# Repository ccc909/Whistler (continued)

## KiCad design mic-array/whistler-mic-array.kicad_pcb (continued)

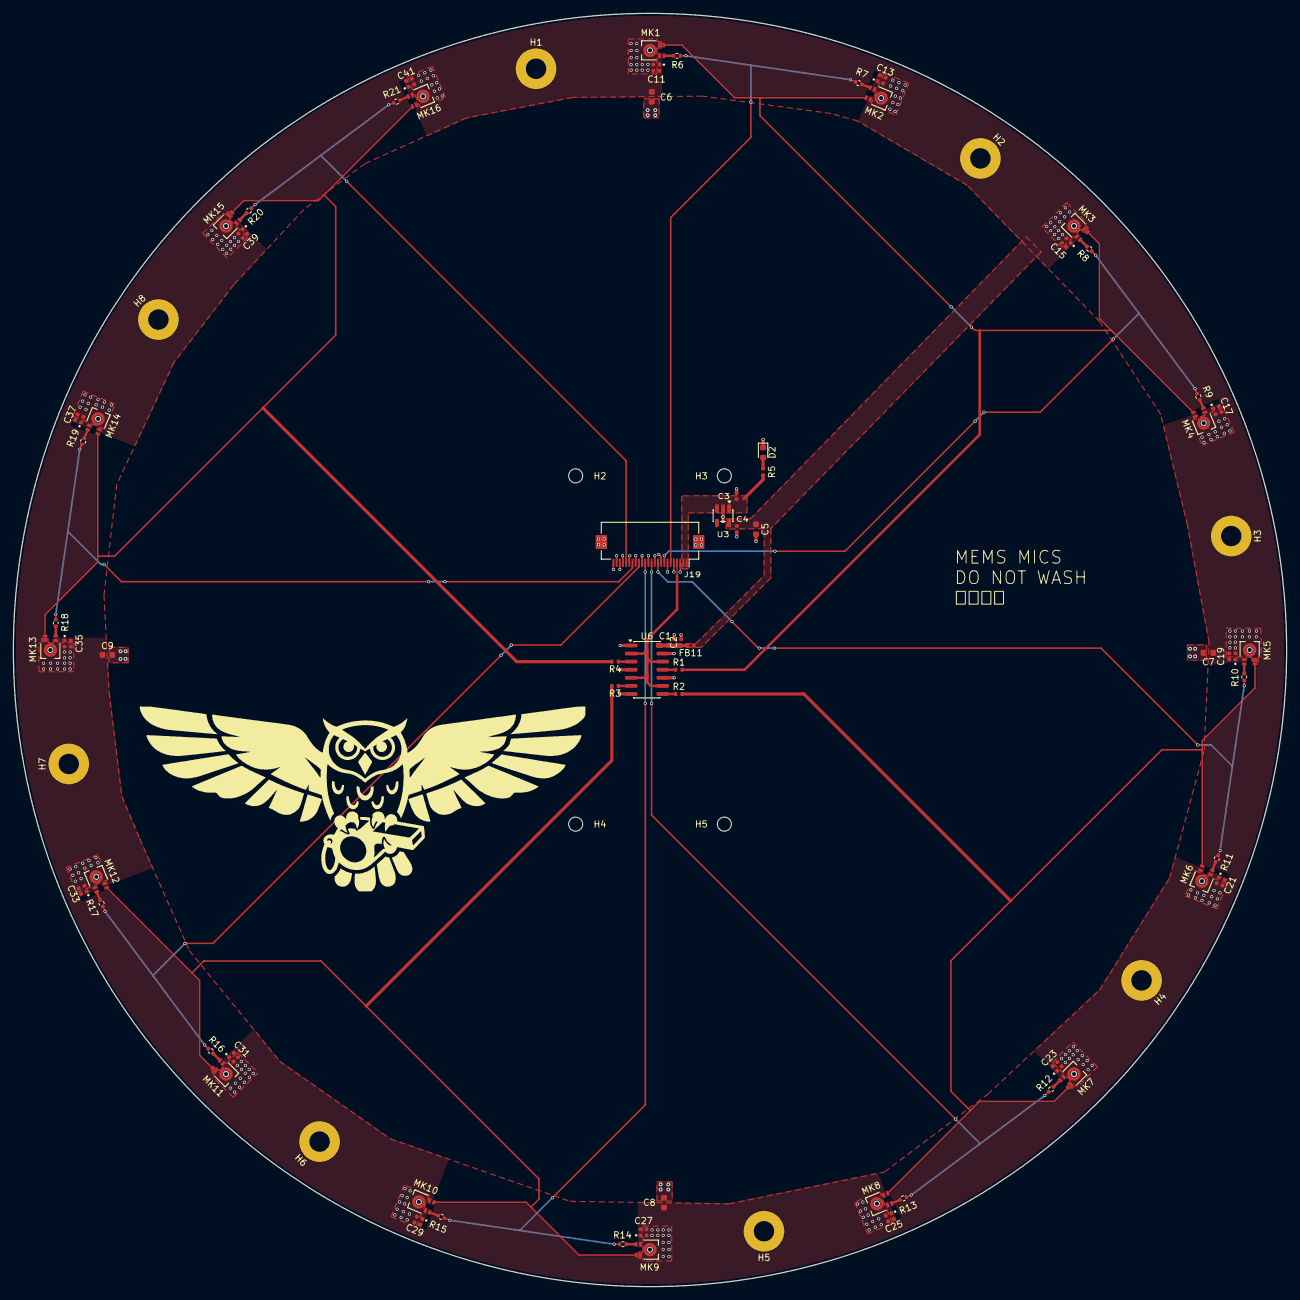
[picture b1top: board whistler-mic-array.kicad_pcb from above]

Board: 2 copper layers, 200.0 x 200.0 mm, 95 parts (0 on the bottom side), 38 nets.

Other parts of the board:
H2#2, H5#2: MountingHole_Pad; MountingHole_3.2mm_M3_Pad
H3#2, H4#2: MountingHole; MountingHole_2.2mm_M2

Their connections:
GND: H2#2.1 (1_1), H5#2.1 (1_1); also elsewhere on the board

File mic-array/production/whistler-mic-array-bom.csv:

Comment,Designator,Footprint,LCSC,Quantity,Manufacturer,MPN,Description
100nF,"C1,C12,C14,C16,C18,C20,C22,C24,C26,C28,C30,C32,C34,C36,C38,C40,C42",C_0402_1005Metric,C1525,17,,,"Unpolarized capacitor, small symbol"
1uF,"C2,C3,C4,C11,C13,C15,C17,C19,C21,C23,C25,C27,C29,C31,C33,C35,C37,C39,C41",C_0402_1005Metric,C14445,19,,,"Unpolarized capacitor, small symbol"
10uF,C5,C_0603_1608Metric,C18800,1,,,Unpolarized capacitor
4.7uF,"C6,C7,C8,C9",C_0603_1608Metric,C1705,4,,,Unpolarized capacitor
LED,D2,LED_0603_1608Metric,C12624,1,,,Light emitting diode
680R,FB11,C_0402_1005Metric,C96691,1,,,"Ferrite bead, small symbol"
Conn_01x24,J19,Hirose_FH12-24S-0.5SH_1x24-1MP_P0.50mm_Horizontal,C202112,1,,,"Generic connector, single row, 01x24, script generated (kicad-library-utils/schlib/autogen/connector/)"
IM72D128V01XTMA1,"MK1,MK2,MK3,MK4,MK5,MK6,MK7,MK8,MK9,MK10,MK11,MK12,MK13,MK14,MK15,MK16",MIC_IM72D128V01XTMA1,C5119248,16,Infineon Technologies,IM72D128,"20 Hz ~ 19 kHz Digital, PDM Microphone MEMS (Silicon) 1.62 V ~ 3.6 V Omnidirectional (-36dB ±1dB @ 94dB SPL) Solder Pads"
22R,"R1,R2,R3,R4",R_0402_1005Metric,C25092,4,,,"Resistor, small symbol"
470R,R5,R_0402_1005Metric,C25117,1,,,"Resistor, small symbol"
33R,"R6,R7,R8,R9,R10,R11,R12,R13,R14,R15,R16,R17,R18,R19,R20,R21",R_0402_1005Metric,C25105,16,,,"Resistor, small symbol"
TPS7A2018PDBVR,U3,SOT-23-5,C963430,1,,,"300 mA Low Dropout Voltage Regulator, Fixed Output, 1.6..6.0Vin, Low-Noise (7μV RMS), 6.5μA IQ LDO, SOT-23"
74LVC125,U6,SOIC-14_3.9x8.7mm_P1.27mm,C6057,1,,,Quad buffer 3-State outputs

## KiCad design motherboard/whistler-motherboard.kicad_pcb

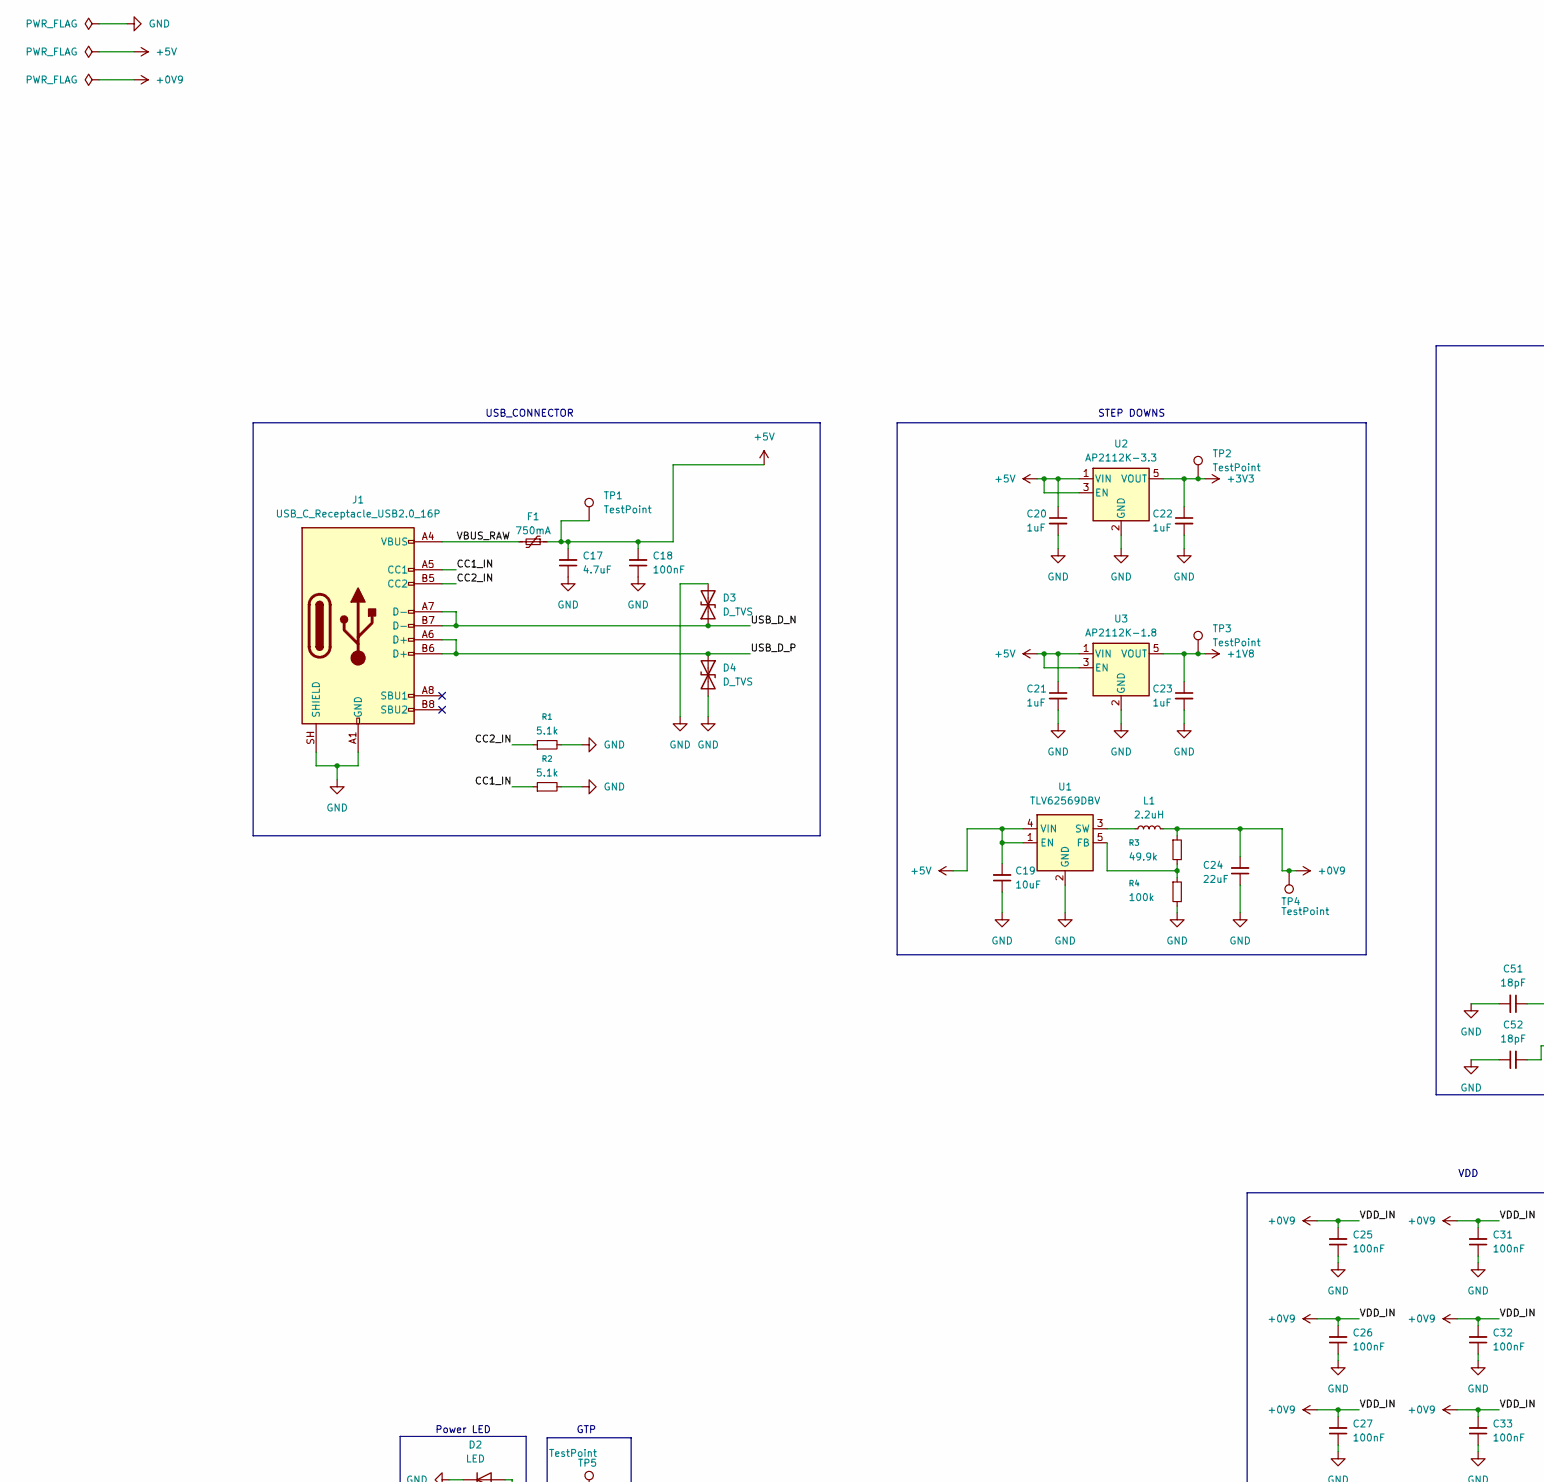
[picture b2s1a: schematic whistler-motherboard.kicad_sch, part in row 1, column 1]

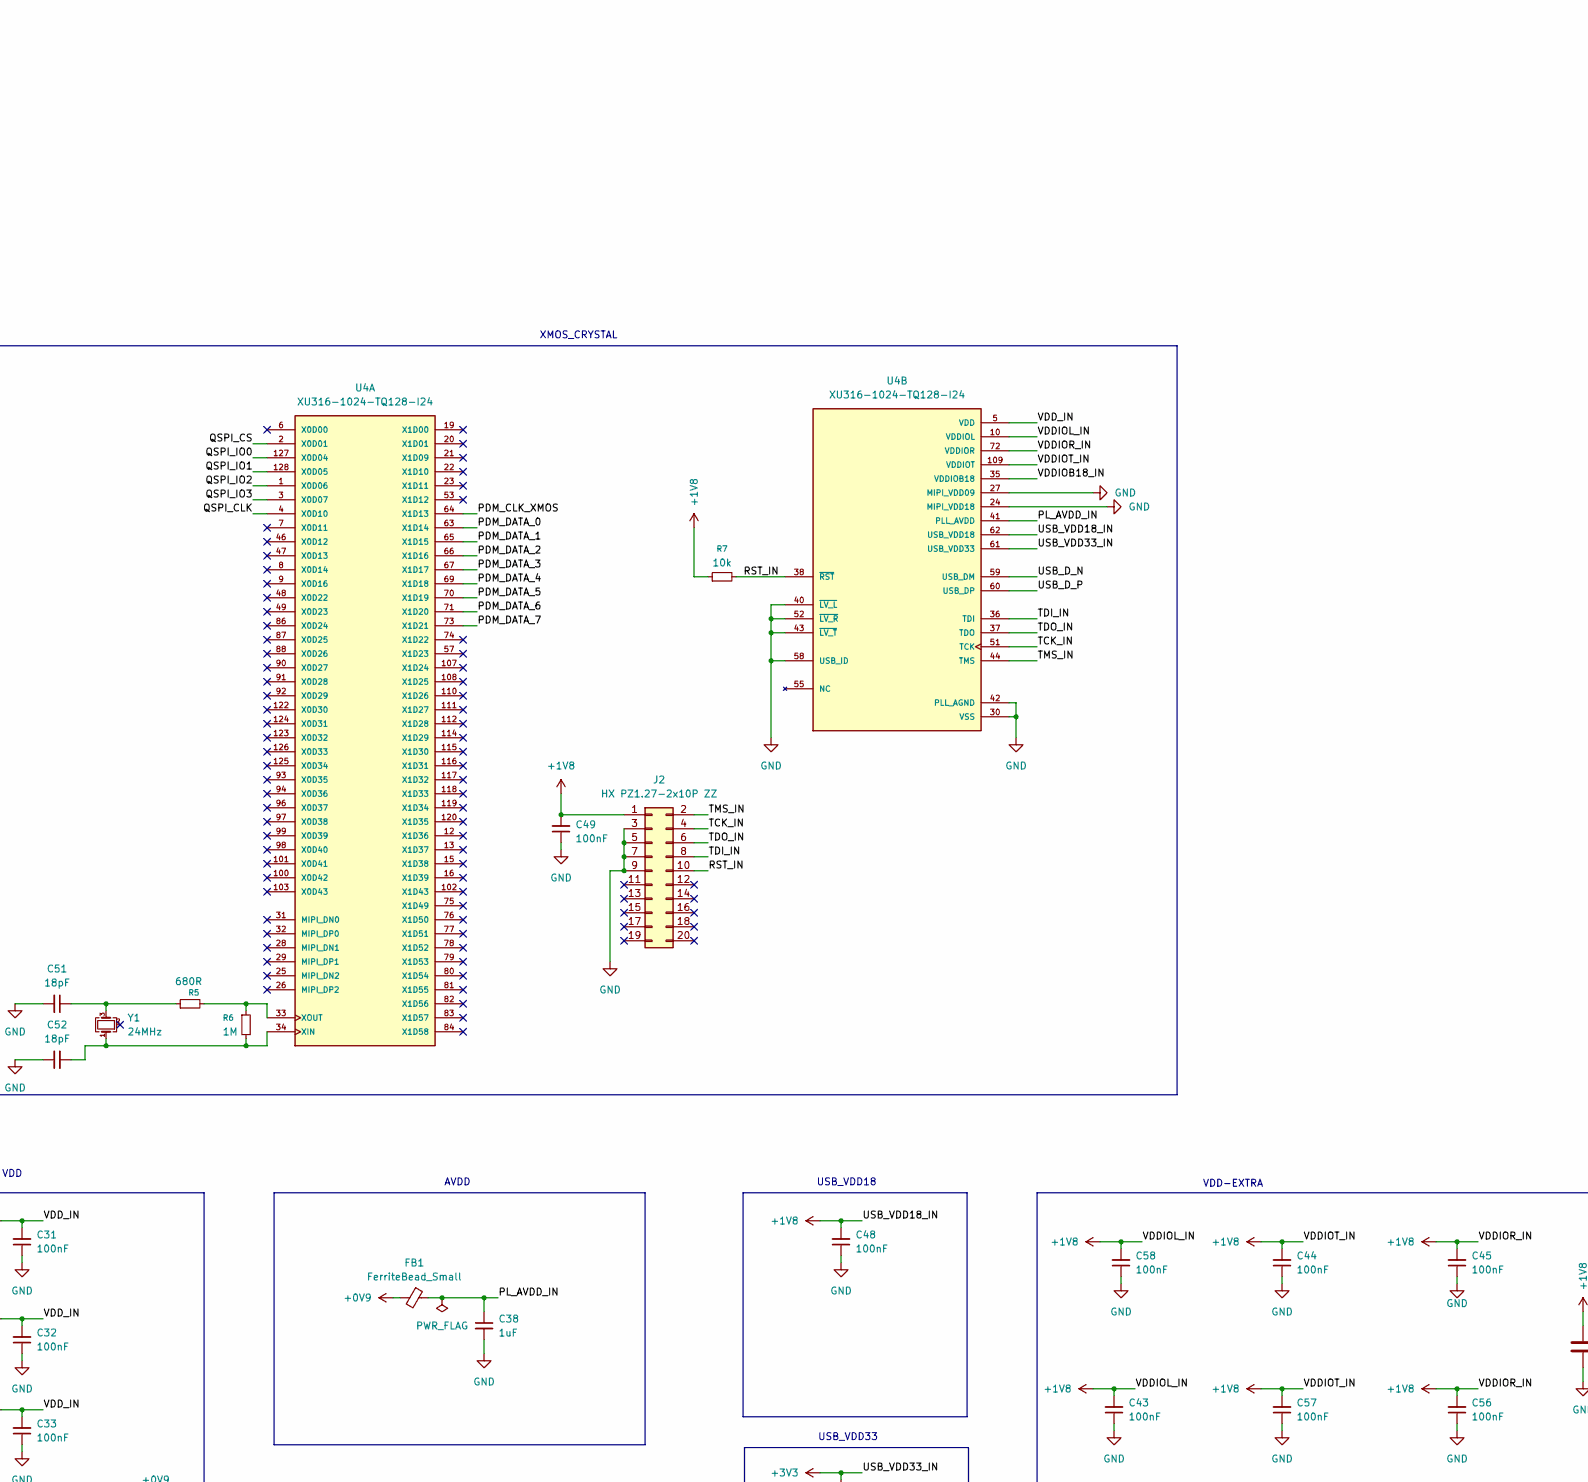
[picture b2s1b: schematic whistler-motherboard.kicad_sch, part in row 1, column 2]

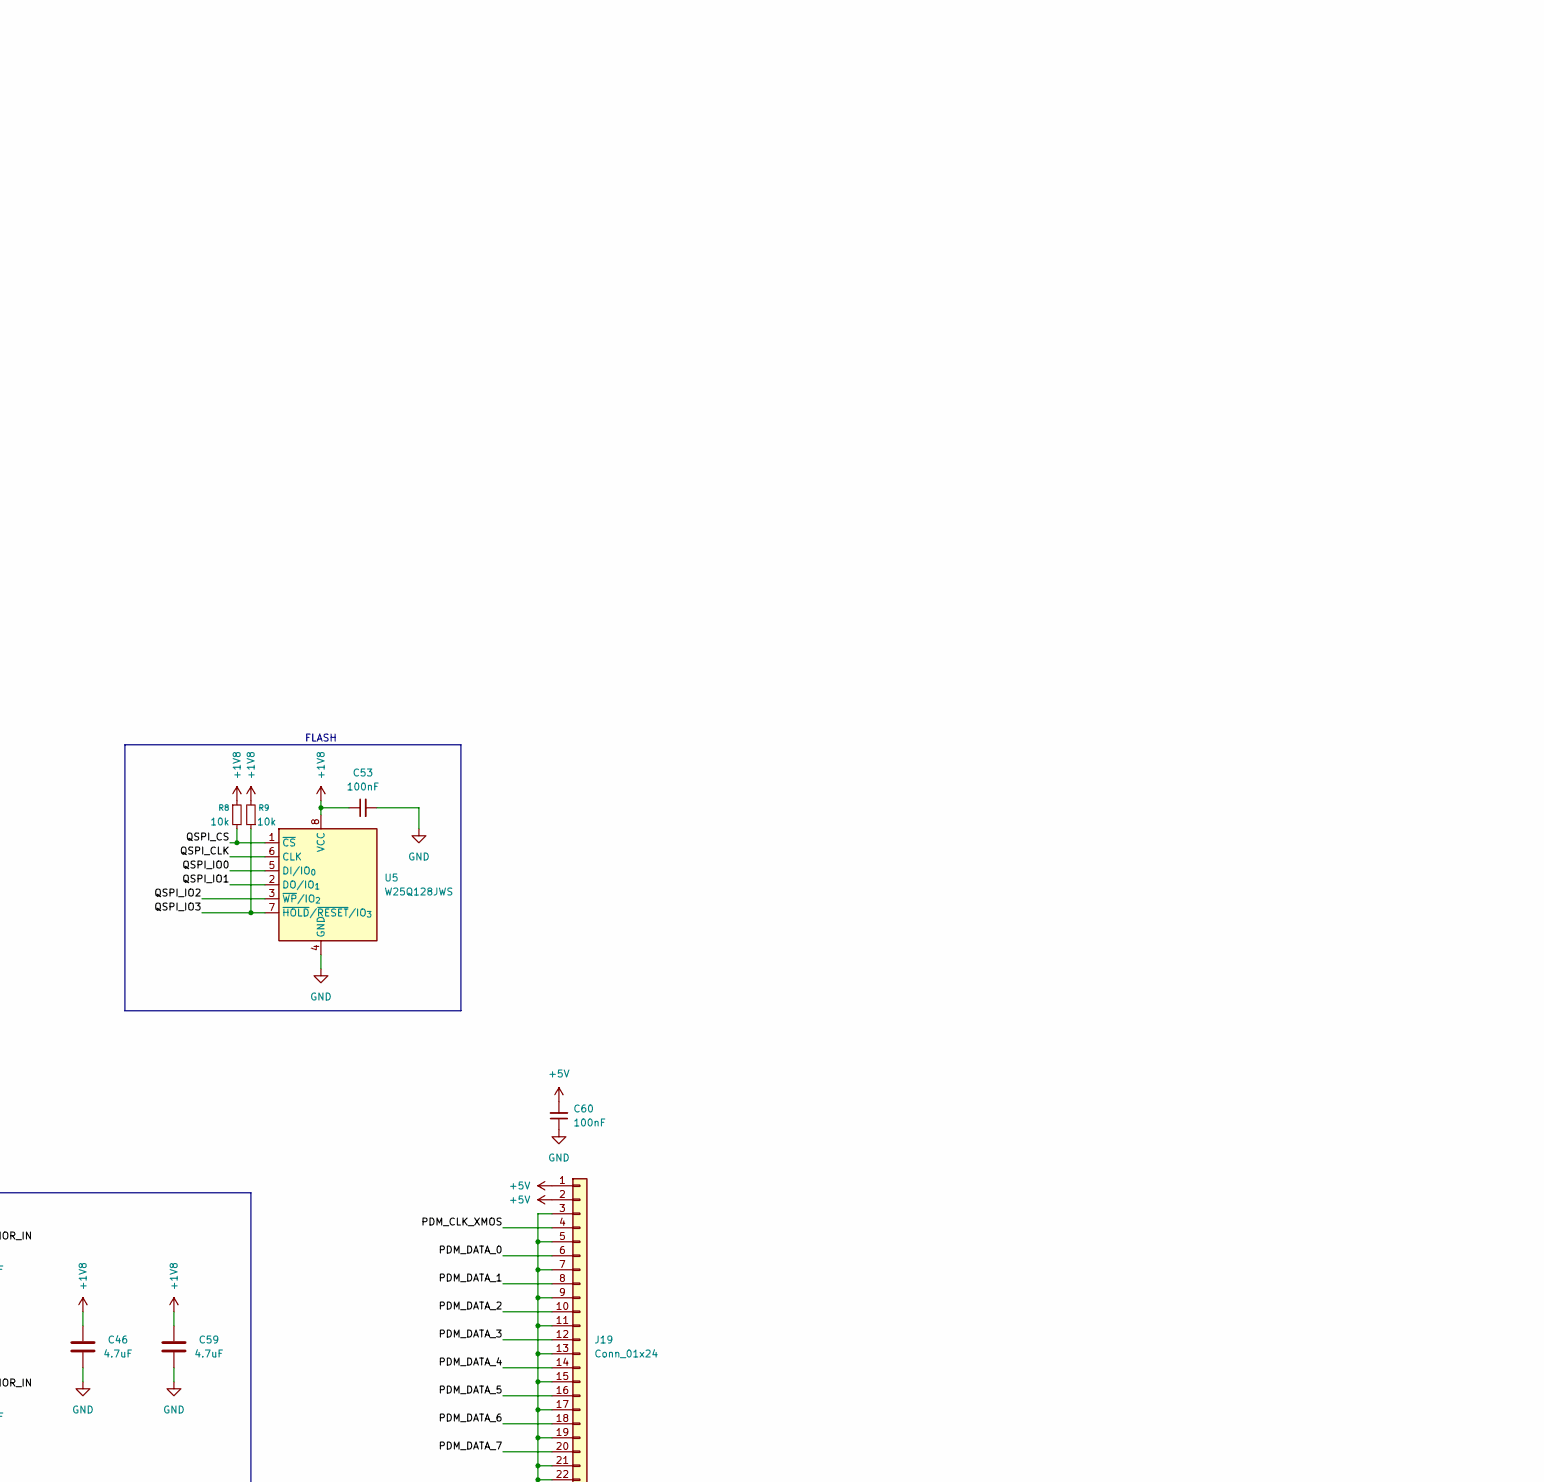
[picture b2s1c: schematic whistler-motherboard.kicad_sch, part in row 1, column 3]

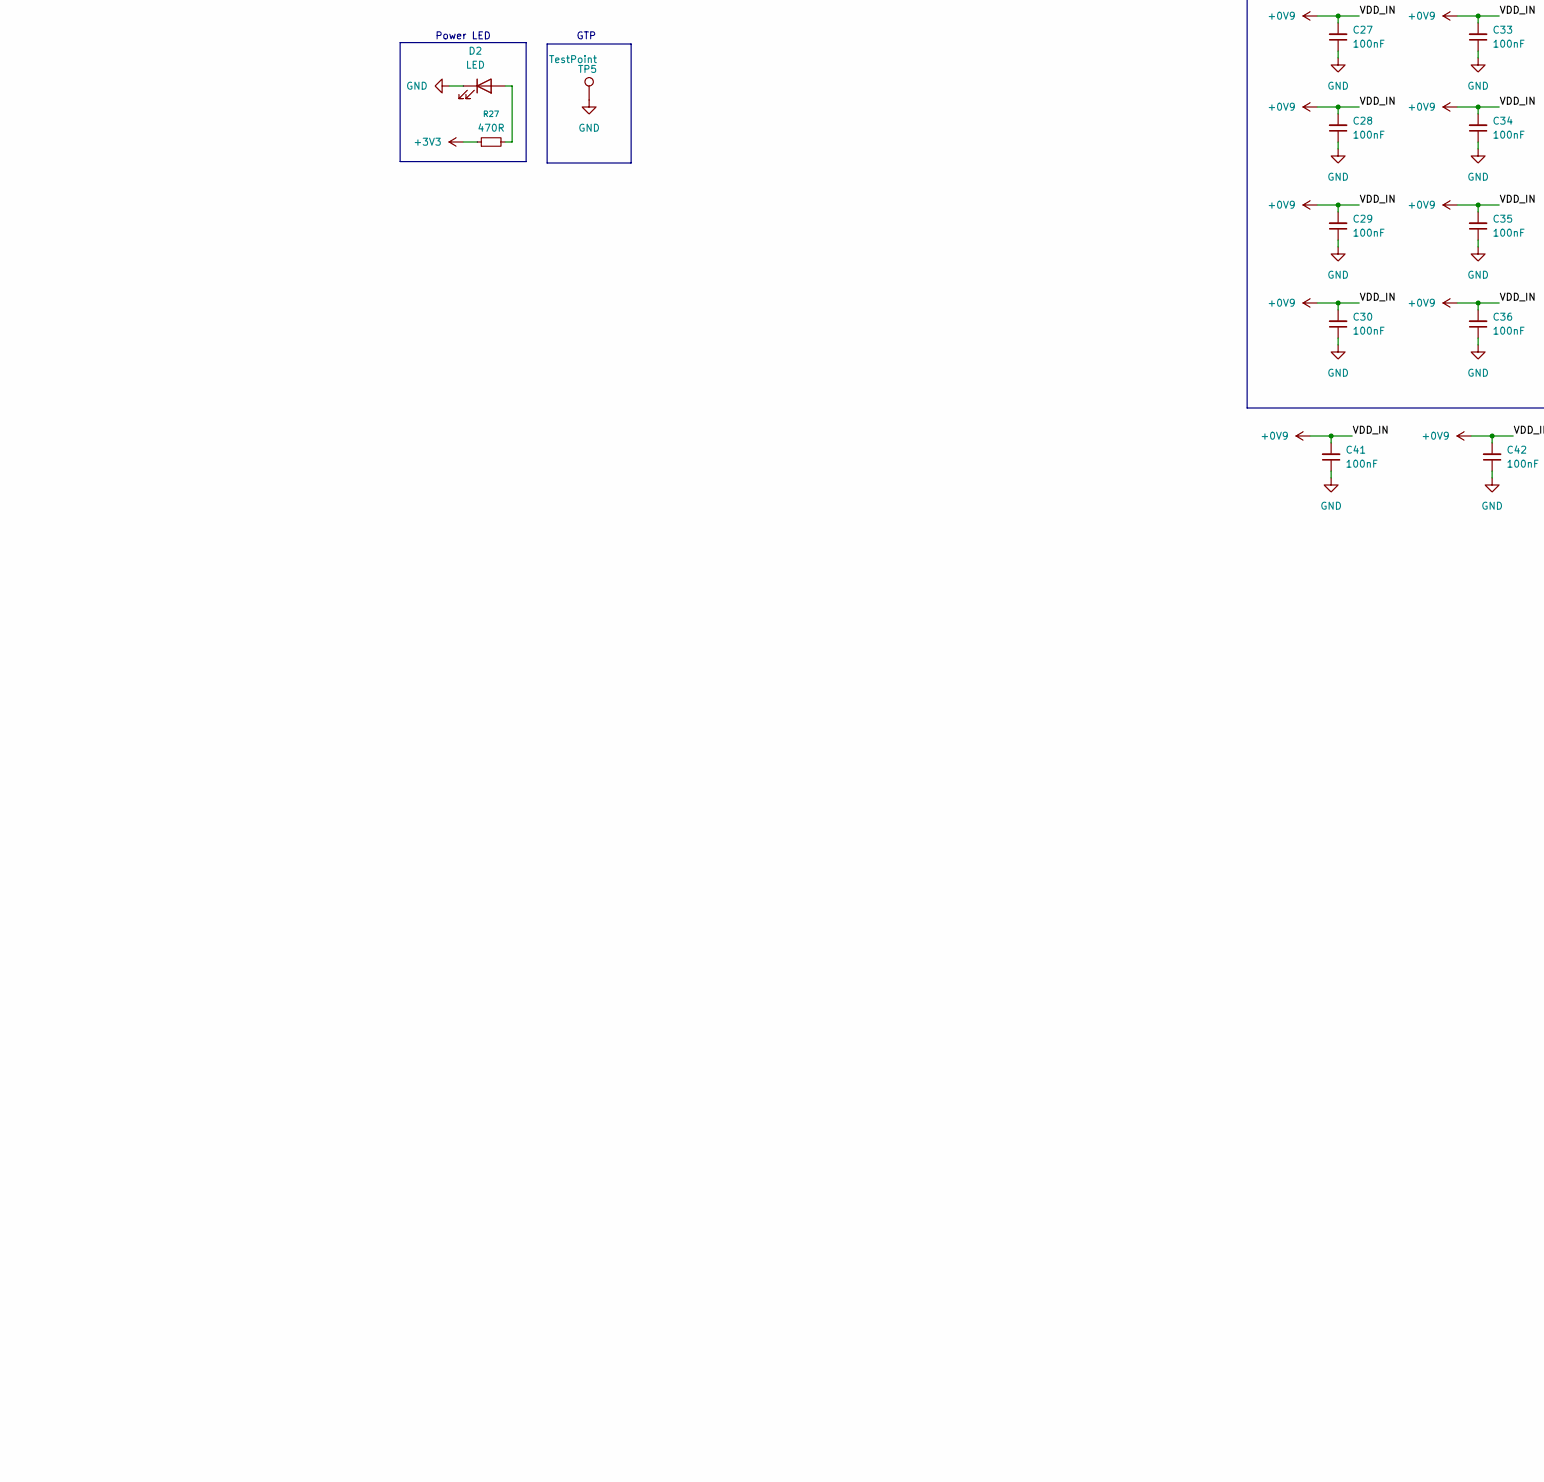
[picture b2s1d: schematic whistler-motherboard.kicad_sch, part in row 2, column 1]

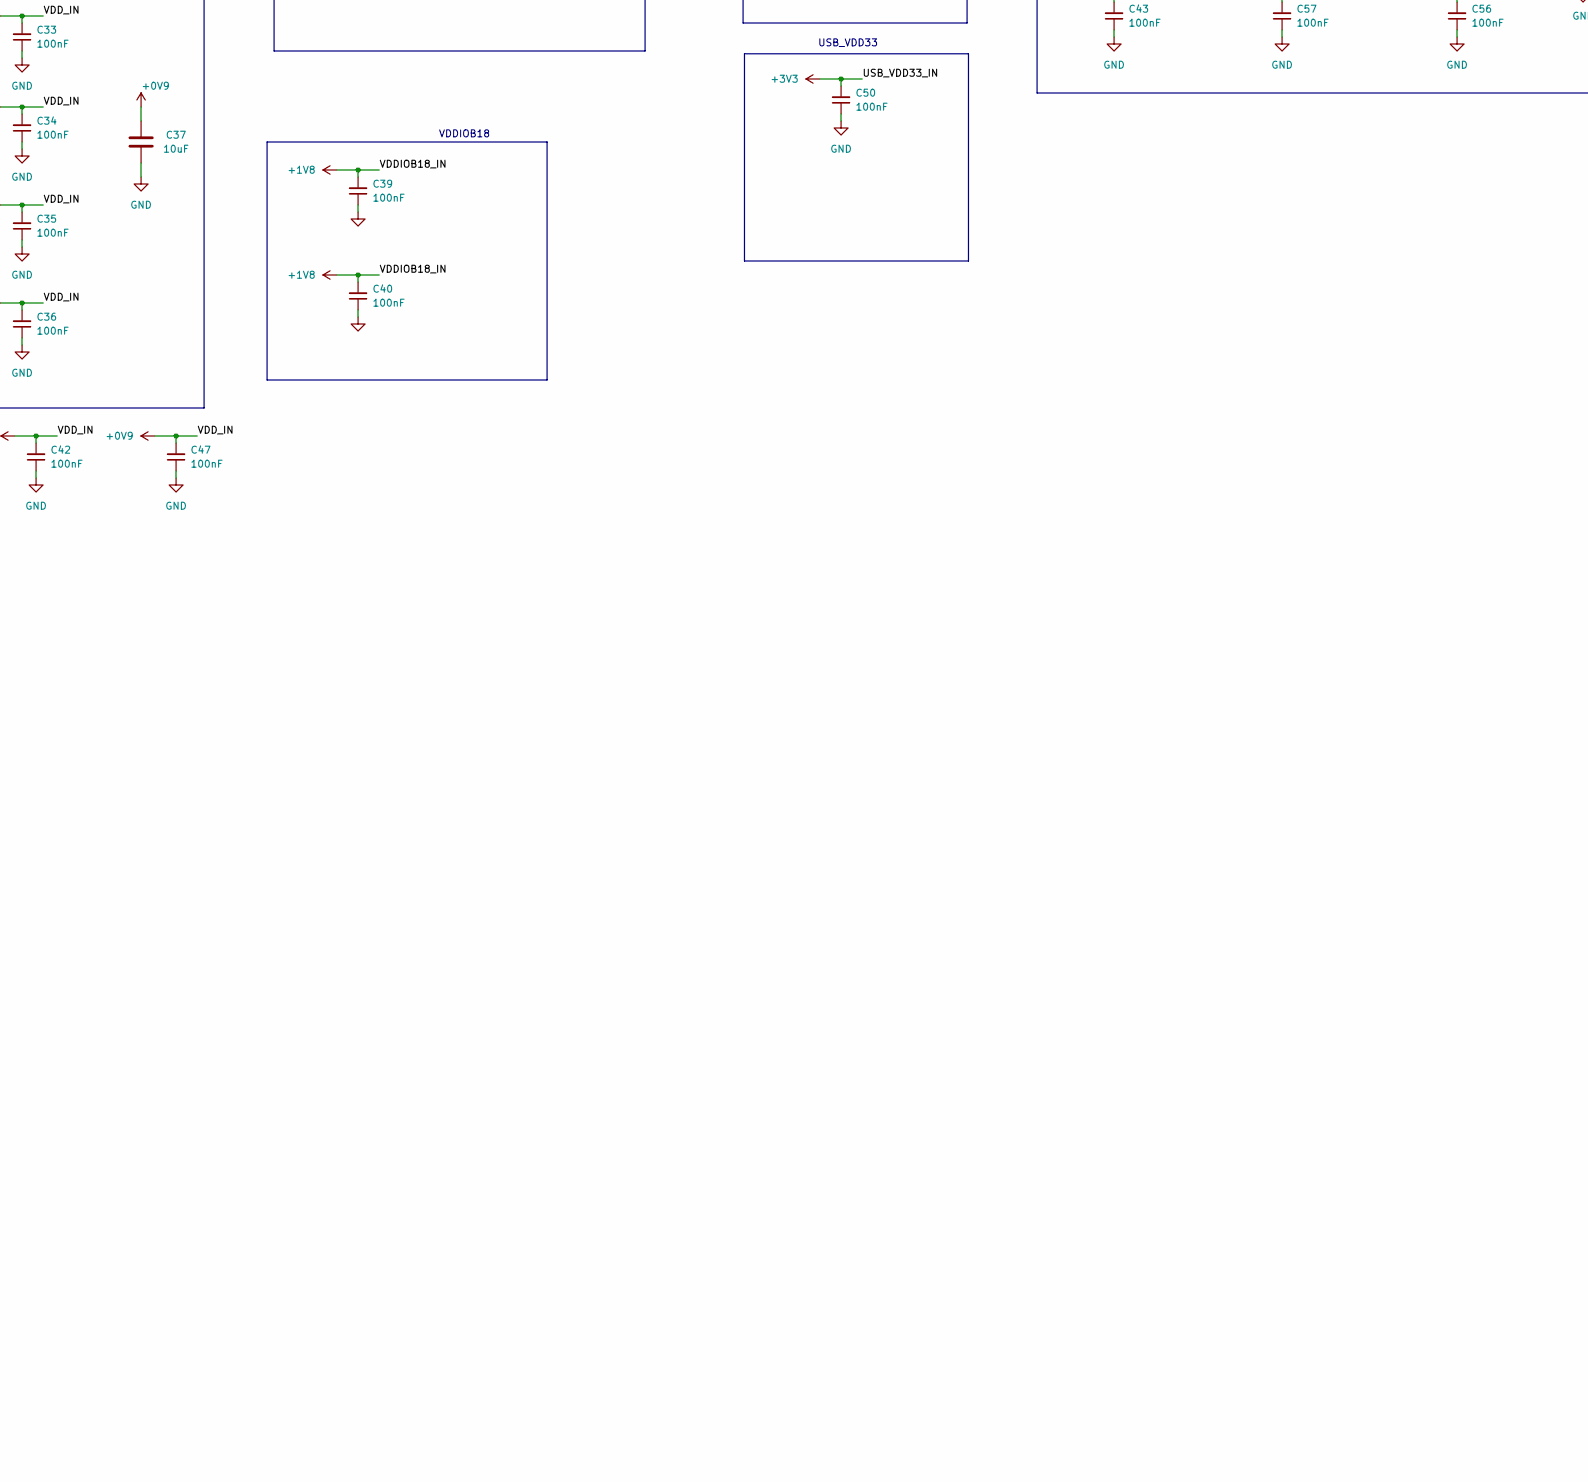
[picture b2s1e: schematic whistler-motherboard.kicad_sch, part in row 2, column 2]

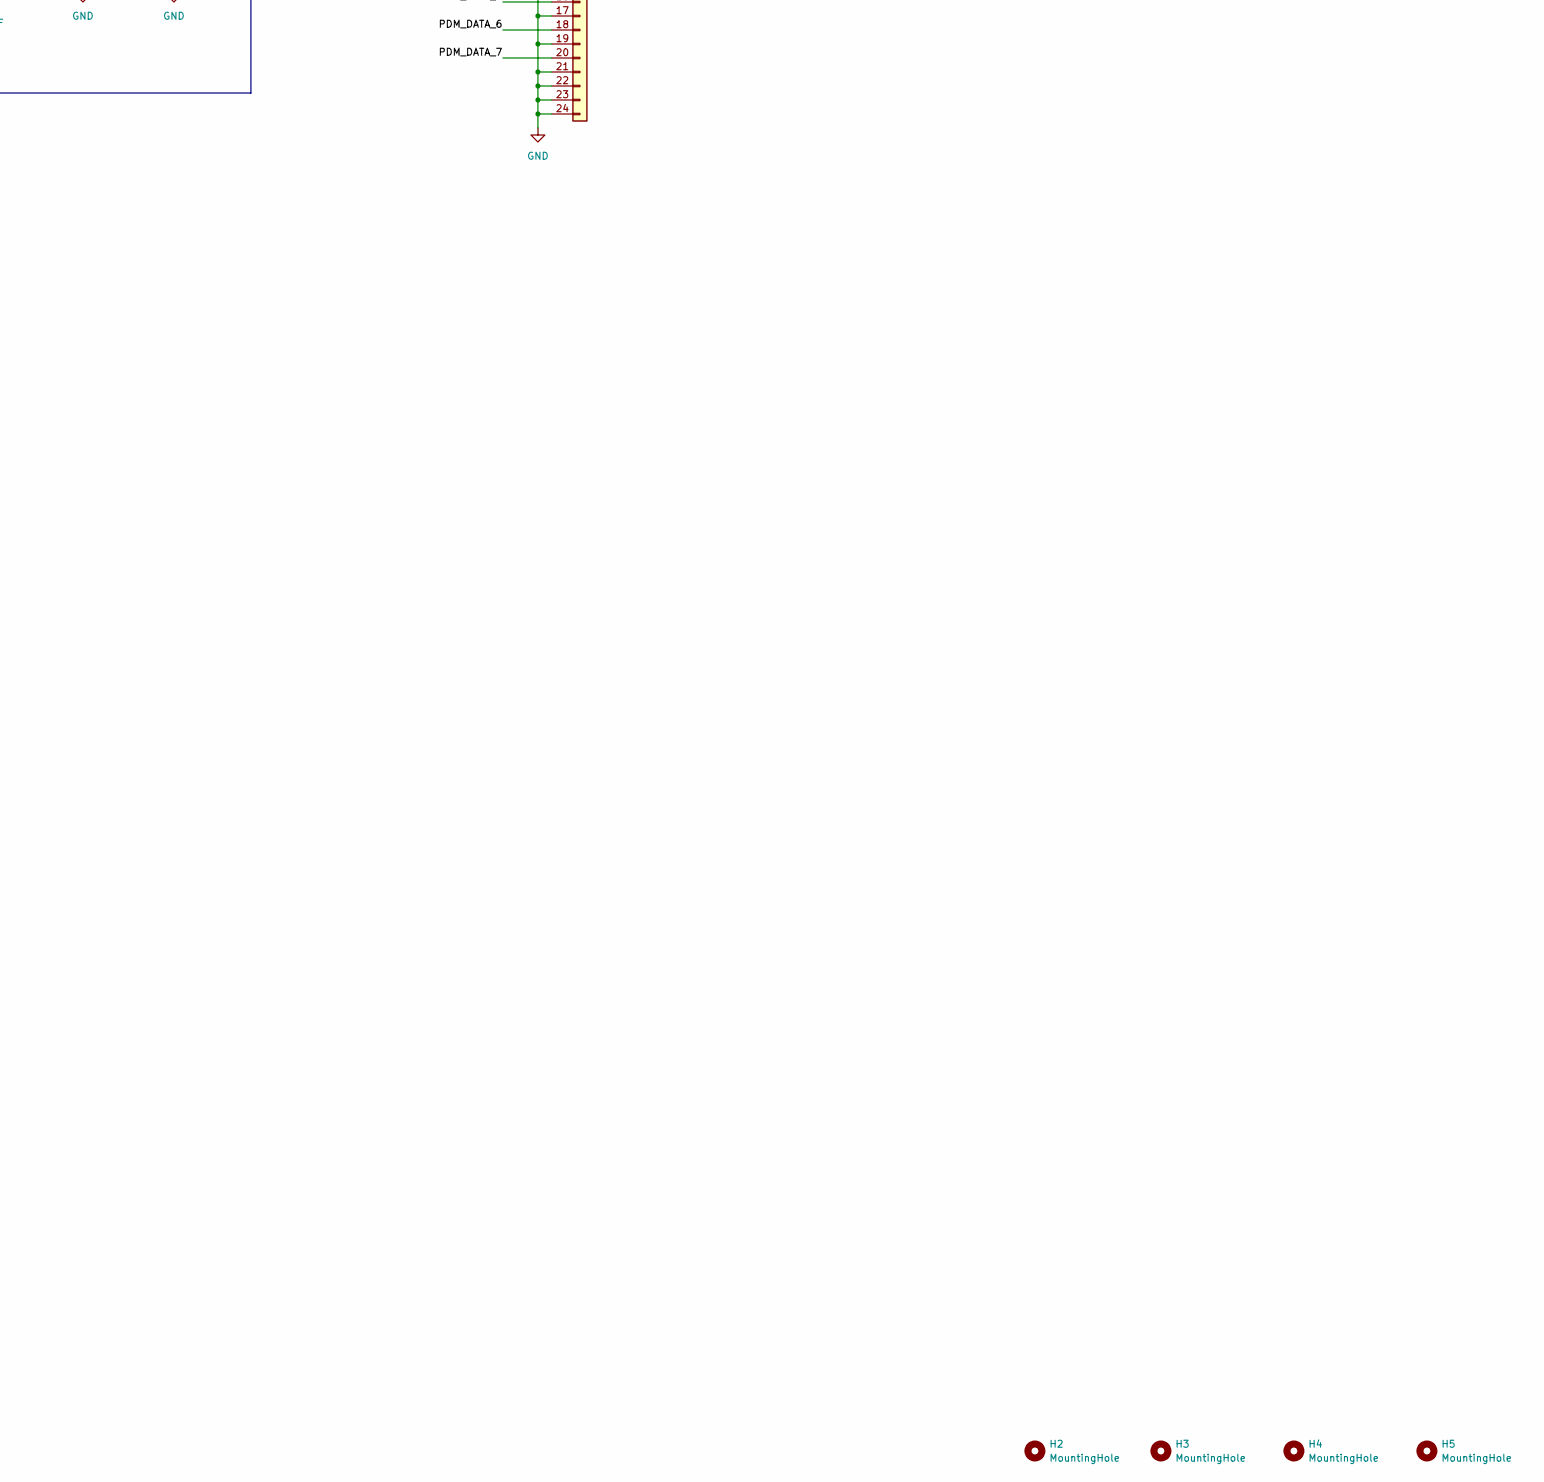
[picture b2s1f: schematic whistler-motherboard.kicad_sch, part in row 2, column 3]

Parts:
C17, C46, C59: 4.7uF; C_0603_1608Metric; LCSC C1705
C18, C25, C26, C27, C28, C29, C30, C31, C32, C33, C34, C35, C36, C39, C40, C41, C42, C43, C44, C45, C47, C48, C49, C50, C53, C56, C57, C58, C60: 100nF; C_0402_1005Metric; LCSC C1525
C19, C37: 10uF; C_0603_1608Metric; LCSC C96446
C20, C21, C22, C23, C38: 1uF; C_0402_1005Metric; LCSC C52923
C24: 22uF; C_0603_1608Metric; LCSC C109448
C51, C52: 18pF; C_0402_1005Metric; LCSC C1549
D2: LED; LED_0603_1608Metric; LCSC C2289
D3, D4: D_TVS; D_0402_1005Metric; LCSC C558615
F1: 750mA; Fuse_1206_3216Metric; LCSC C371166
FB1: FerriteBead_Small; L_0603_1608Metric; LCSC C85833
H2, H3, H4, H5: MountingHole; MountingHole_2.2mm_M2
J1: USB_C_Receptacle_USB2.0_16P; USB_C_Receptacle_GCT_USB4105-xx-A_16P_TopMnt_Horizontal; LCSC C3025063
J2: HX PZ1.27-2x10P ZZ; PinHeader_2x10_P1.27mm_Vertical; LCSC C22438125
J19: Conn_01x24; Hirose_FH12-24S-0.5SH_1x24-1MP_P0.50mm_Horizontal; LCSC C202112
L1: 2.2uH; INDC2016X120N; LCSC C337893
R1, R2: 5.1k; R_0402_1005Metric; LCSC C25905
R3: 49.9k; R_0402_1005Metric; LCSC C137969
R4: 100k; R_0402_1005Metric; LCSC C25741
R5: 680R; R_0402_1005Metric; LCSC C25130
R6: 1M; R_0402_1005Metric; LCSC C26083
R7, R8, R9: 10k; R_0402_1005Metric; LCSC C25744
R27: 470R; R_0402_1005Metric; LCSC C25117
TP1, TP2, TP3, TP4, TP5: TestPoint; TestPoint_Pad_1.0x1.0mm
U1: TLV62569DBV; SOT-23-5; LCSC C141836
U2: AP2112K-3.3; SOT-23-5; LCSC C23380830
U3: AP2112K-1.8; SOT-23-5; LCSC C3021123
U4: XU316-1024-TQ128-I24; QFP40P1600X1600X120-129N; PARTREV 2025/1/13; LCSC C6938291
U5: W25Q128JWS; SOIC-8_5.3x5.3mm_P1.27mm; LCSC C2763561
Y1: 24MHz; Crystal_SMD_3225-4Pin_3.2x2.5mm; LCSC C70590

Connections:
+0V9: C24.2, C25.2, C26.2, C27.2, C28.2, C29.2, C30.2, C31.2, C32.2, C33.2, C34.2, C35.2, C36.2, C37.1, C41.2, C42.2, C47.2, FB1.2, L1.2, R3.1, TP4.1 (1_1), U4.5 (VDD), U4.11 (VDD), U4.14 (VDD), U4.18 (VDD), U4.39 (VDD), U4.45 (VDD), U4.50 (VDD), U4.54 (VDD), U4.68 (VDD), U4.85 (VDD), U4.95 (VDD), U4.104 (VDD), U4.105 (VDD), U4.106 (VDD), U4.113 (VDD)
+1V8: C23.1, C39.2, C40.2, C43.2, C44.2, C45.2, C46.1, C48.2, C49.2, C53.1, C56.2, C57.2, C58.2, C59.1, J2.1, R7.1, R8.1, R9.2, TP3.1 (1_1), U3.5 (VOUT), U4.10 (VDDIOL), U4.17 (VDDIOL), U4.35 (VDDIOB18), U4.56 (VDDIOB18), U4.62 (USB_VDD18), U4.72 (VDDIOR), U4.89 (VDDIOR), U4.109 (VDDIOT), U4.121 (VDDIOT), U5.8 (VCC)
+3V3: C22.1, C50.2, R27.1, TP2.1 (1_1), U2.5 (VOUT), U4.61 (USB_VDD33)
+5V: C17.2, C18.2, C19.2, C20.1, C21.1, C60.2, F1.1, J19.1, J19.2, TP1.1 (1_1), U1.1 (EN), U1.4 (VIN), U2.1 (VIN), U2.3 (EN), U3.1 (VIN), U3.3 (EN)
/CC1_IN: J1.A5 (CC1), R2.1
/CC2_IN: J1.B5 (CC2), R1.1
/PDM_CLK_XMOS: J19.4, U4.64 (X1D13)
/PDM_DATA_0: J19.6, U4.63 (X1D14)
/PDM_DATA_1: J19.8, U4.65 (X1D15)
/PDM_DATA_2: J19.10, U4.66 (X1D16)
/PDM_DATA_3: J19.12, U4.67 (X1D17)
/PDM_DATA_4: J19.14, U4.69 (X1D18)
/PDM_DATA_5: J19.16, U4.70 (X1D19)
/PDM_DATA_6: J19.18, U4.71 (X1D20)
/PDM_DATA_7: J19.20, U4.73 (X1D21)
/PL_AVDD_IN: C38.1, FB1.1, U4.41 (PLL_AVDD)
/QSPI_CLK: U4.4 (X0D10), U5.6 (CLK)
/QSPI_CS: R8.2, U4.2 (X0D01), U5.1 (~CS)
/QSPI_IO0: U4.127 (X0D04), U5.5 (DI/IO_{0})
/QSPI_IO1: U4.128 (X0D05), U5.2 (DO/IO_{1})
/QSPI_IO2: U4.1 (X0D06), U5.3 (~WP/IO_{2})
/QSPI_IO3: R9.1, U4.3 (X0D07), U5.7 (~HOLD/~RESET/IO_{3})
/RST_IN: J2.10, R7.2, U4.38 (~RST)
/TCK_IN: J2.4, U4.51 (TCK)
/TDI_IN: J2.8, U4.36 (TDI)
/TDO_IN: J2.6, U4.37 (TDO)
/TMS_IN: J2.2, U4.44 (TMS)
/USB_D_N: D3.1 (A1), J1.A7 (D-), J1.B7 (D-), U4.59 (USB_DM)
/USB_D_P: D4.1 (A1), J1.A6 (D+), J1.B6 (D+), U4.60 (USB_DP)
/VBUS_RAW: F1.2, J1.A4 (VBUS), J1.A9 (VBUS), J1.B4 (VBUS), J1.B9 (VBUS)
GND: C17.1, C18.1, C19.1, C20.2, C21.2, C22.2, C23.2, C24.1, C25.1, C26.1, C27.1, C28.1, C29.1, C30.1, C31.1, C32.1, C33.1, C34.1, C35.1, C36.1, C37.2, C38.2, C39.1, C40.1, C41.1, C42.1, C43.1, C44.1, C45.1, C46.2, C47.1, C48.1, C49.1, C50.1, C51.2, C52.1, C53.2, C56.1, C57.1, C58.1, C59.2, C60.1, D2.1 (K), D3.2 (A2), D4.2 (A2), J1.A1 (GND), J1.A12 (GND), J1.B1 (GND), J1.B12 (GND), J1.SH (SHIELD), J2.3, J2.5, J2.7, J2.9, J19.3, J19.5, J19.7, J19.9, J19.11, J19.13, J19.15, J19.17, J19.19, J19.21, J19.22, J19.23, J19.24, R1.2, R2.2, R4.2, TP5.1 (1_1), U1.2 (GND), U2.2 (GND), U3.2 (GND), U4.24 (MIPI_VDD18), U4.27 (MIPI_VDD09), U4.30 (VSS), U4.40 (~LV_L), U4.42 (PLL_AGND), U4.43 (~LV_T), U4.52 (~LV_R), U4.58 (USB_ID), U4.129 (VSS), U5.4 (GND)
unnamed: C51.1, R5.1, Y1.3
unnamed: D2.2 (A), R27.2
unnamed: R3.2, R4.1, U1.5 (FB)
unnamed: L1.1, U1.3 (SW)
unnamed: C52.2, R6.2, U4.34 (XIN), Y1.1
unnamed: R5.2, R6.1, U4.33 (XOUT)

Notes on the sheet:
USB_CONNECTOR
STEP DOWNS
FLASH
VDDIOB18
VDD-EXTRA
USB_VDD33
AVDD
GTP
Power LED
XMOS_CRYSTAL
USB_VDD18
VDD

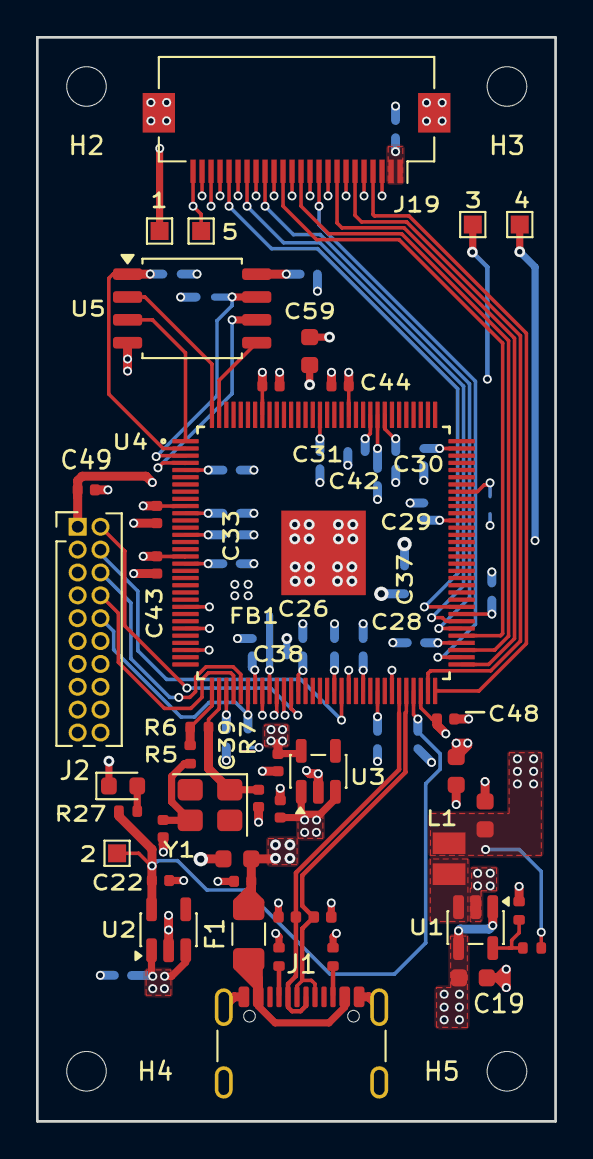
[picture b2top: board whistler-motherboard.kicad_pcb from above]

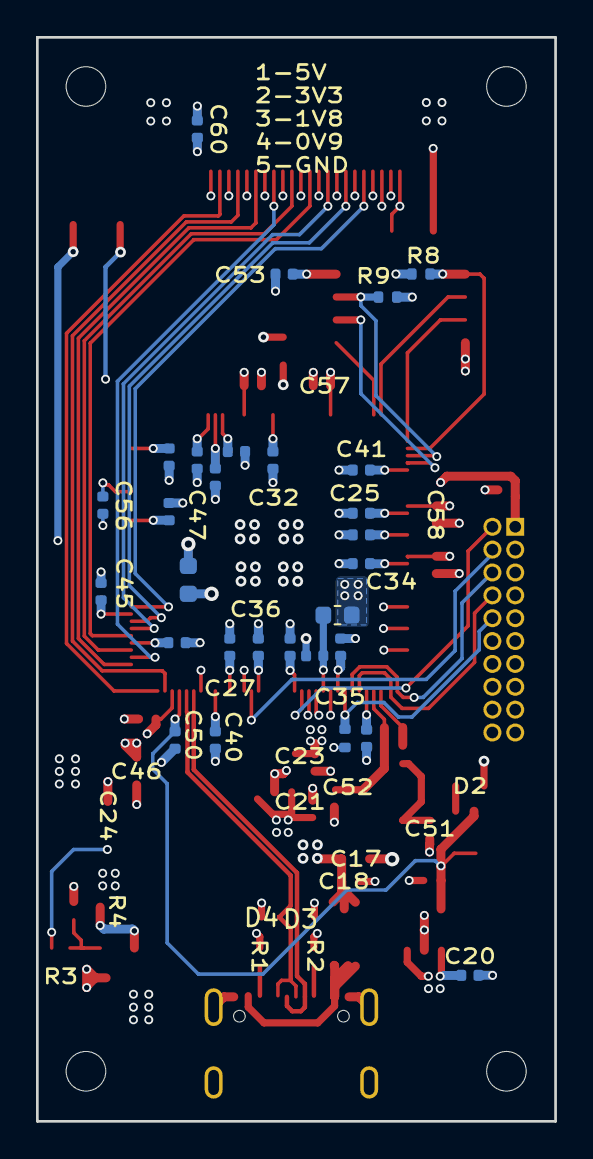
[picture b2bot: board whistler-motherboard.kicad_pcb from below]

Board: 4 copper layers, 28.8 x 60.2 mm, 76 parts (29 on the bottom side), 37 nets.

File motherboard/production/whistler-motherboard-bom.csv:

Comment,Designator,Footprint,LCSC,Quantity,Manufacturer,MPN,Description
4.7uF,"C17,C46,C59",C_0603_1608Metric,C1705,3,,,"Unpolarized capacitor,Unpolarized capacitor, small symbol"
100nF,"C18,C25,C26,C27,C28,C29,C30,C31,C32,C33,C34,C35,C36,C39,C40,C41,C42,C43,C44,C45,C47,C48,C49,C50,C53,C56,C57,C58,C60",C_0402_1005Metric,C1525,29,,,"Unpolarized capacitor, small symbol"
10uF,"C19,C37",C_0603_1608Metric,C96446,2,,,"Unpolarized capacitor,Unpolarized capacitor, small symbol"
1uF,"C20,C21,C22,C23,C38",C_0402_1005Metric,C52923,5,,,"Unpolarized capacitor, small symbol"
22uF,C24,C_0603_1608Metric,C109448,1,,,"Unpolarized capacitor, small symbol"
18pF,"C51,C52",C_0402_1005Metric,C1549,2,,,"Unpolarized capacitor, small symbol"
LED,D2,LED_0603_1608Metric,C2289,1,,,Light emitting diode
D_TVS,"D3,D4",D_0402_1005Metric,C558615,2,,,Bidirectional transient-voltage-suppression diode
750mA,F1,Fuse_1206_3216Metric,C371166,1,,,"Resettable fuse, polymeric positive temperature coefficient, small symbol"
FerriteBead_Small,FB1,L_0603_1608Metric,C85833,1,,,"Ferrite bead, small symbol"
USB_C_Receptacle_USB2.0_16P,J1,USB_C_Receptacle_GCT_USB4105-xx-A_16P_TopMnt_Horizontal,C3025063,1,,,USB 2.0-only 16P Type-C Receptacle connector
HX PZ1.27-2x10P ZZ,J2,PinHeader_2x10_P1.27mm_Vertical,C22438125,1,,,"Generic connector, double row, 02x10, odd/even pin numbering scheme (row 1 odd numbers, row 2 even numbers), script generated (kicad-library-utils/schlib/autogen/connector/)"
Conn_01x24,J19,Hirose_FH12-24S-0.5SH_1x24-1MP_P0.50mm_Horizontal,C202112,1,,,"Generic connector, single row, 01x24, script generated (kicad-library-utils/schlib/autogen/connector/)"
2.2uH,L1,INDC2016X120N,C337893,1,,,"Inductor, small symbol"
5.1k,"R1,R2",R_0402_1005Metric,C25905,2,,,"Resistor, small symbol"
49.9k,R3,R_0402_1005Metric,C137969,1,,,"Resistor, small symbol"
100k,R4,R_0402_1005Metric,C25741,1,,,"Resistor, small symbol"
680R,R5,R_0402_1005Metric,C25130,1,,,"Resistor, small symbol"
1M,R6,R_0402_1005Metric,C26083,1,,,"Resistor, small symbol"
10k,"R7,R8,R9",R_0402_1005Metric,C25744,3,,,"Resistor, small symbol"
470R,R27,R_0402_1005Metric,C25117,1,,,"Resistor, small symbol"
TLV62569DBV,U1,SOT-23-5,C141836,1,,,"High Efficiency Synchronous Buck Converter, Adjustable Output 0.6V-5.5V, 2A, SOT-23-5"
AP2112K-3.3,U2,SOT-23-5,C23380830,1,,,"600mA low dropout linear regulator, with enable pin, 3.8V-6V input voltage range, 3.3V fixed positive output, SOT-23-5"
AP2112K-1.8,U3,SOT-23-5,C3021123,1,,,"600mA low dropout linear regulator, with enable pin, 2.5V-6V input voltage range, 1.8V fixed positive output, SOT-23-5"
XU316-1024-TQ128-I24,U4,QFP40P1600X1600X120-129N,C6938291,1,XMOS,XU316-1024-TQ128-I24,XCore xcore.ai Microcontroller IC 32-Bit 16-Core 2400MIPs 8KB (8K x 8) OTP 128-TQFP (14x14)
W25Q128JWS,U5,SOIC-8_5.3x5.3mm_P1.27mm,C2763561,1,,,"128Mbit / 16MiB Serial Flash Memory, Standard/Dual/Quad SPI, 2.7-3.6V, SOIC-8"
24MHz,Y1,Crystal_SMD_3225-4Pin_3.2x2.5mm,C70590,1,,,"Four pin crystal, GND on pins 2 and 4, small symbol"
